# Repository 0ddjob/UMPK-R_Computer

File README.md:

# УМПК-Р (UMPK-R) Computer
Information about the Soviet Ukrainian computer based on the Soviet homebrew computer called the [РАДИО-86РК](https://github.com/skiselev/radio-86rk) (RADIO-86RK).  I'll refer to it as the "RK" (Radio Computer) for the rest of this description.  This computer utilised the Soviet equivalent of the Intel 8080A called the КР580ВМ80А.<br>

УМПК-Р = Универсальный МикроПроцессорный Комплект - Радио (Universal MicroProcessor Kit - Radio)<br>

My computer doesn't work so I need to troubleshoot, hence this translation work.  The Soviets were very good in including schematics & documentation how the computer works.<br>

There were quite a few industrially produced clones of the RK design so understanding how it works can help with troubleshooting other machines.<br>

## My YouTube Videos (As of 9-Mar-2025)
- [Part 1: First Look](https://youtu.be/Kr2Yl7z__qQ)
- [Part 2: Trying to get video output](https://youtu.be/anAznSh7gso)
- [Part 3: Video output troubleshooting continues](https://youtu.be/vZf2vCqavNA)
- [Part 4: Faulty DRAM?](https://youtu.be/Y1xS1cXXh0Q)
- [Part 5: Progress, Maybe](https://youtu.be/lffw-Pr39o8)
- [Part 6: Quick Troubleshooting Update](https://youtu.be/sxfEuDL6Sj8)
- [Part 7: New Keyboard](https://youtu.be/CkGMiSZlumM)

## [English Documentation](/Documentation_ENG)
I have done a partial translation (thanks to Grok) of the Operation Manual - original scanned Russian, my cleaned-up Russian and the translated English manuals can be found here.  There are four file types:
- Apple Pages (native)
- PDF
- Rich Text Format
- MS Word

Note that there may be errors in my cleaned-up Russian copy ... some words in the scanned manual disappeared into the page binding!<br>

Question: what on earth is "foiled lavsan" (фольгированный лавсан)?<br>

_"Lavsan" is a Russian trade name for a type of polyester film, chemically known as polyethylene terephthalate (PET). It is similar to materials like Mylar in Western terminology. "Фольгированный" means "foiled" or "coated with foil," indicating that the lavsan film has a thin layer of metal foil (often aluminium) applied to it. In the context of the УМПК-Р keyboard device, this refers to a metallised polyester film used in the membrane keyboard construction, where the foil provides conductive tracks or contacts for key operation._<br>

_So, in technical terms, it could be described as "metallised polyester film" or simply "foiled PET film", depending on the context._

In the English translation I have kept the Soviet/Russian part identifiers rather than transliterate them, but I have included Western equivalent part identifiers as well.<br>

The scanned Russian manual includes the tables & diagrams referred to in the translation.  It also includes a map of the parts on the motherboard.<br>

I have also included some very-roughly machine translated (Google image) pages from the original Soviet RADIO magazine that explain the RK's functionality - I hope to come back and do better translations.<br>

## Memory Layout

## Map of ICs
Due to the complete lack of 14-pin 32kbit DRAMs in the West I have replaced my faulty ones with 4164 64kbit DRAMs.<br>

```
- D1    КР580ГФ24   8224    Clock generator
- D2    КР580ВТ57   8257    DMA controller
- D3    К155ИЕ4     74LS92  Divide-by-12 counter
- D4    К155ЛИ1     74LS08  Quad 2IN AND
- D5    КР580ВМ80А  8080A   CPU
- D6    К155ЛП5     74LS86  Quad 2IN XOR
- D7    К589ИР12    8212    8-bit I/O port
- D8    КР580ВГ75   8275    CRT controller
- D9    К555ИД7     74LS138 1-of-8 decoder/demultiplexer
- D10   К155ЛА8     74LS01  Quad 2IN NAND
- D11   К155ЛН1     74LS04  Hex inverter
- D12   К573РФ2     2716    EPROM (for character data)
- D13   К155ТМ2     74LS74  Dual D-type flip flop
- D14   КР580ВВ55А  8255    Programmable peripheral adaptor
- D15   К155ИР1     74LS95  4-bit shift register
- D16   К155ИР13    74LS198 8-bit shift register
- D17   К555КП11    74LS257 Quad 2IN multiplexer
- D18   К555КП11    74LS257 Quad 2IN multiplexer
- D19   К573РФ5     2716    EPROM (for MONITOR)
- D20   КР565РУ5Д1          32K x 1bit DRAM
- D21   КР565РУ5Д1          32K x 1bit DRAM
- D22   КР565РУ5Д1          32K x 1bit DRAM
- D23   КР565РУ5Д1          32K x 1bit DRAM
- D24   КР580ВВ55А  8255    Programmable peripheral adaptor
- D25   КР565РУ5Д1          32K x 1bit DRAM
- D26   КР565РУ5Д1          32K x 1bit DRAM
- D27   КР565РУ5Д1          32K x 1bit DRAM
- D28   КР565РУ5Д1          32K x 1bit DRAM
- D29   К553УД2     LM301   Op. Amp.
```
## [Replacement Keyboard](/Replacement_Keyboard)
I suspect that after 40-odd years (mid-1980s to mid-2020s) that the "foiled lavsan" membrane keyboard has started to malfunction.  To replace it I have designed a new board using Cherry MX keyswitches.  You will need to recover the СНП58-32 connector and the speaker from the original keyboard PCB, otherwise it uses readily available parts.<br>

My initial design doesn't re-use the black, clip-on fascia - it expects you to have just the plain, naked PCB ... that's my preference.  But I guess it would be good to design one for the fascia as well ... <br>

### Status
24-Mar-2025: Submitted to PCBWAY for fabrication
20-Apr-2025: Built first board, mostly okay, some revisions required

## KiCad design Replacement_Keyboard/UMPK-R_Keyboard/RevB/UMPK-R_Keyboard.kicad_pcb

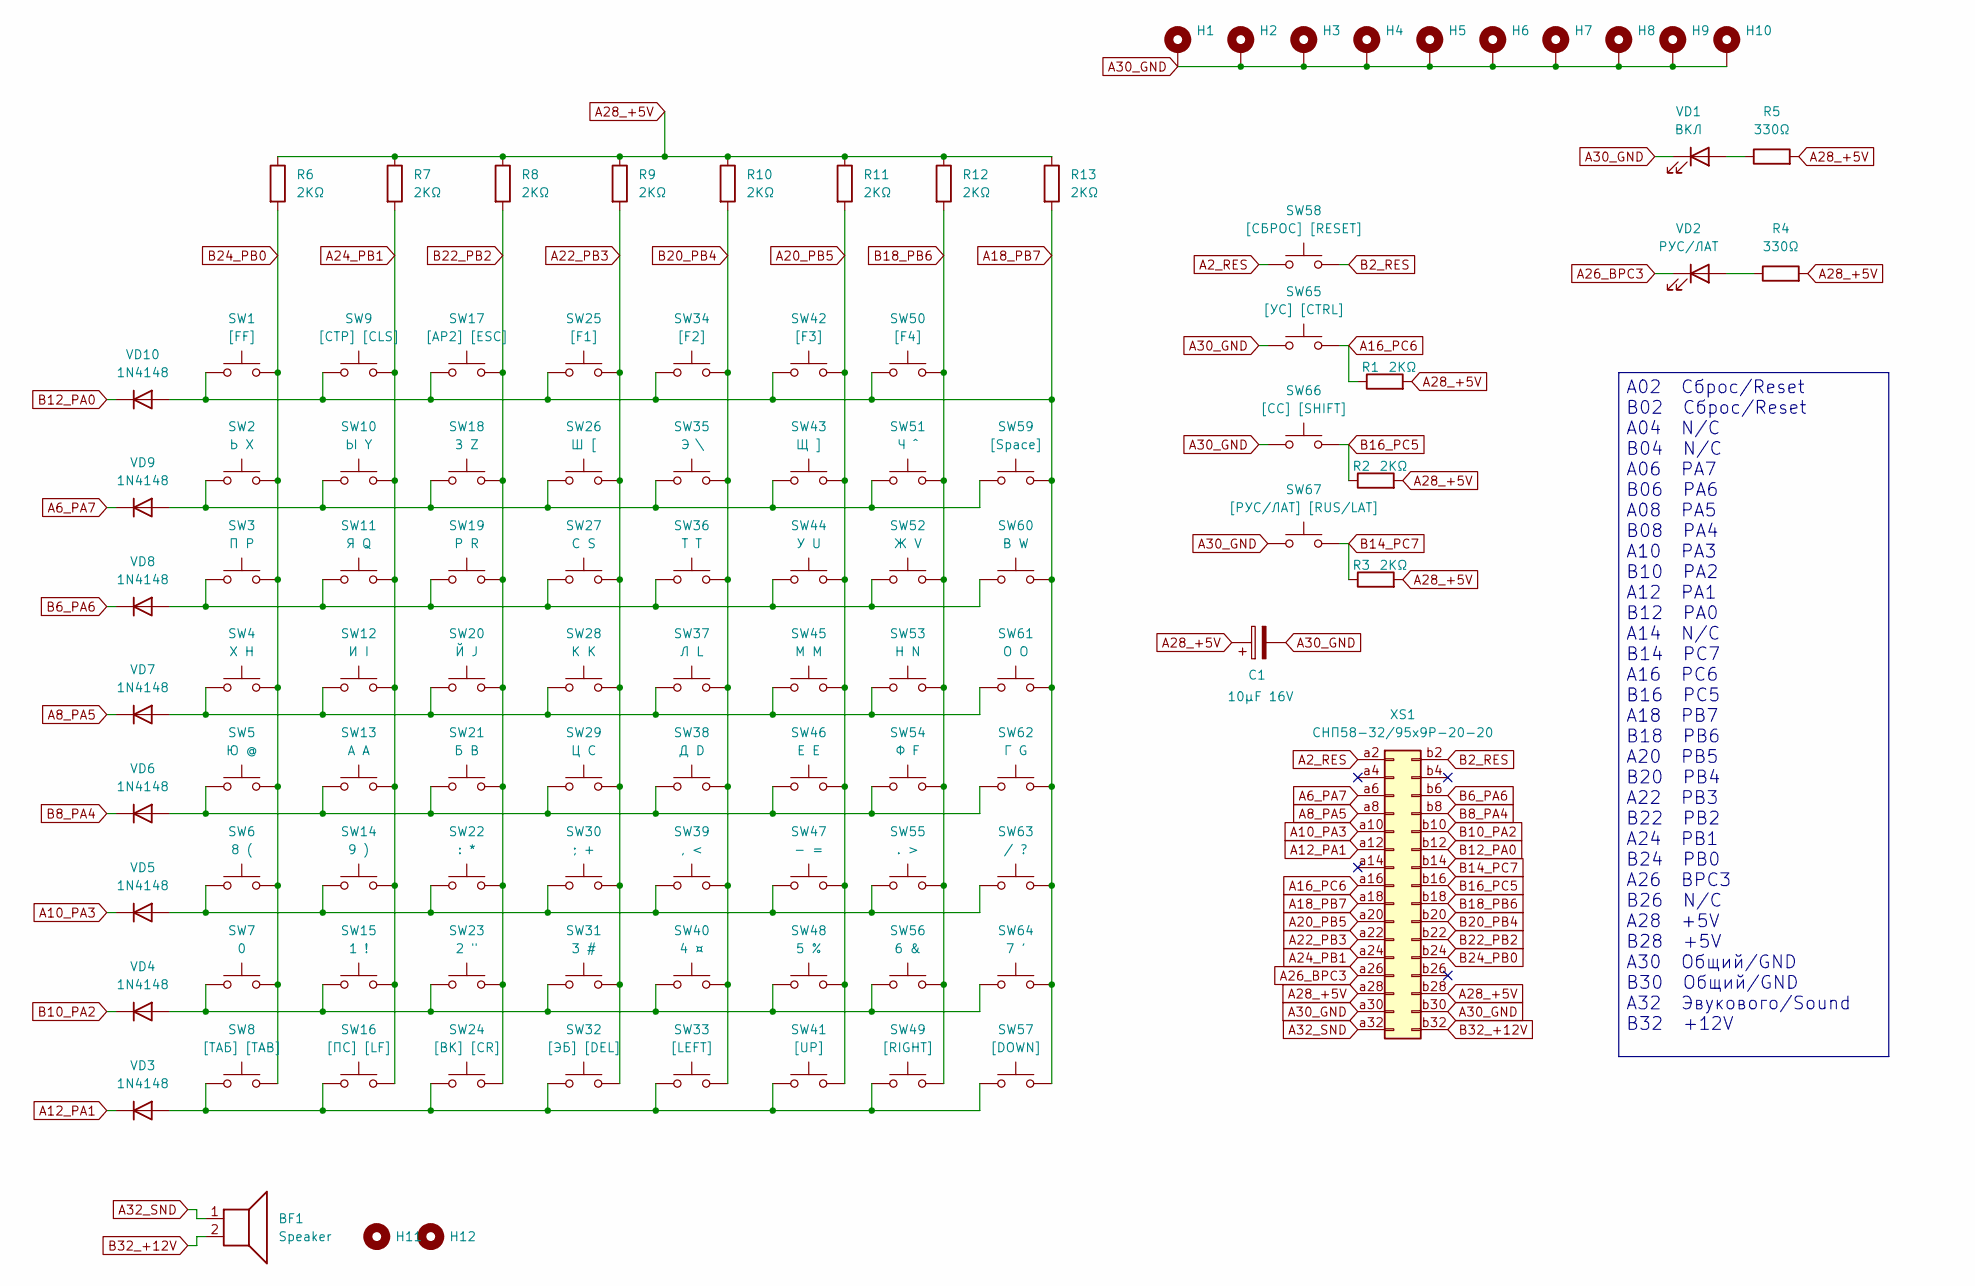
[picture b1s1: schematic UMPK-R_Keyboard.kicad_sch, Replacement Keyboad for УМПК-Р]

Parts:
BF1: Speaker; PinHeader_1x02_P2.54mm_Vertical
C1: 10µF 16V; CP_Radial_D5.0mm_P2.50mm
H1, H2, H3, H4, H5, H6, H7, H8, H9, H10: MountingHole_Pad; MountingHole_3.2mm_M3_Pad
H11, H12: MountingHole; MountingHole_3.2mm_M3
R1, R2, R3, R6, R7, R8, R9, R10, R11, R12, R13: 2KΩ; R_Axial_DIN0207_L6.3mm_D2.5mm_P7.62mm_Horizontal
R4, R5: 330Ω; R_Axial_DIN0207_L6.3mm_D2.5mm_P7.62mm_Horizontal
SW1: [FF]; SW_Cherry_MX_PCB_1.00u
SW2: Ь X; SW_Cherry_MX_PCB_1.00u
SW3: П P; SW_Cherry_MX_PCB_1.00u
SW4: Х H; SW_Cherry_MX_PCB_1.00u
SW5: Ю @; SW_Cherry_MX_PCB_1.00u
SW6: 8 (; SW_Cherry_MX_PCB_1.00u
SW7: 0; SW_Cherry_MX_PCB_1.00u
SW8: [ТАБ] [TAB]; SW_Cherry_MX_PCB_1.00u
SW9: [СТР] [CLS]; SW_Cherry_MX_PCB_1.00u
SW10: Ы Y; SW_Cherry_MX_PCB_1.00u
SW11: Я Q; SW_Cherry_MX_PCB_1.00u
SW12: И I; SW_Cherry_MX_PCB_1.00u
SW13: А A; SW_Cherry_MX_PCB_1.00u
SW14: 9 ); SW_Cherry_MX_PCB_1.00u
SW15: 1 !; SW_Cherry_MX_PCB_1.00u
SW16: [ПС] [LF]; SW_Cherry_MX_PCB_1.00u
SW17: [АР2] [ESC]; SW_Cherry_MX_PCB_1.00u
SW18: З Z; SW_Cherry_MX_PCB_1.00u
SW19: Р R; SW_Cherry_MX_PCB_1.00u
SW20: Й J; SW_Cherry_MX_PCB_1.00u
SW21: Б B; SW_Cherry_MX_PCB_1.00u
SW22: : *; SW_Cherry_MX_PCB_1.00u
SW23: 2 "; SW_Cherry_MX_PCB_1.00u
SW24: [ВК] [CR]; SW_Cherry_MX_PCB_2.00u
SW25: [F1]; SW_Cherry_MX_PCB_1.00u
SW26: Ш [; SW_Cherry_MX_PCB_1.00u
SW27: С S; SW_Cherry_MX_PCB_1.00u
SW28: К K; SW_Cherry_MX_PCB_1.00u
SW29: Ц C; SW_Cherry_MX_PCB_1.00u
SW30: ; +; SW_Cherry_MX_PCB_1.00u
SW31: 3 #; SW_Cherry_MX_PCB_1.00u
SW32: [ЭБ] [DEL]; SW_Cherry_MX_PCB_1.00u
SW33: [LEFT]; SW_Cherry_MX_PCB_1.00u
SW34: [F2]; SW_Cherry_MX_PCB_1.00u
SW35: Э \; SW_Cherry_MX_PCB_1.00u
SW36: Т T; SW_Cherry_MX_PCB_1.00u
SW37: Л L; SW_Cherry_MX_PCB_1.00u
SW38: Д D; SW_Cherry_MX_PCB_1.00u
SW39: , <; SW_Cherry_MX_PCB_1.00u
SW40: 4 ¤; SW_Cherry_MX_PCB_1.00u
SW41: [UP]; SW_Cherry_MX_PCB_1.00u
SW42: [F3]; SW_Cherry_MX_PCB_1.00u
SW43: Щ ]; SW_Cherry_MX_PCB_1.00u
SW44: У U; SW_Cherry_MX_PCB_1.00u
SW45: М M; SW_Cherry_MX_PCB_1.00u
SW46: Е E; SW_Cherry_MX_PCB_1.00u
SW47: - =; SW_Cherry_MX_PCB_1.00u
SW48: 5 %; SW_Cherry_MX_PCB_1.00u
SW49: [RIGHT]; SW_Cherry_MX_PCB_1.00u
SW50: [F4]; SW_Cherry_MX_PCB_1.00u
SW51: Ч ^; SW_Cherry_MX_PCB_1.00u
SW52: Ж V; SW_Cherry_MX_PCB_1.00u
SW53: Н N; SW_Cherry_MX_PCB_1.00u
SW54: Ф F; SW_Cherry_MX_PCB_1.00u
SW55: . >; SW_Cherry_MX_PCB_1.00u
SW56: 6 &; SW_Cherry_MX_PCB_1.00u
SW57: [DOWN]; SW_Cherry_MX_PCB_1.00u
SW58: [СБРОС] [RESET]; SW_Cherry_MX_PCB_1.00u
SW59: [Space]; SW_Cherry_MX_PCB_2.25u
SW60: В W; SW_Cherry_MX_PCB_1.00u
SW61: О O; SW_Cherry_MX_PCB_1.00u
SW62: Г G; SW_Cherry_MX_PCB_1.00u
SW63: / ?; SW_Cherry_MX_PCB_1.00u
SW64: 7 '; SW_Cherry_MX_PCB_1.00u
SW65: [УС] [CTRL]; SW_Cherry_MX_PCB_1.00u
SW66: [СС] [SHIFT]; SW_Cherry_MX_PCB_1.00u
SW67: [РУС/ЛАТ] [RUS/LAT]; SW_Cherry_MX_PCB_1.00u
VD1: ВКЛ; LED_D5.0mm
VD2: РУС/ЛАТ; LED_D5.0mm
VD3, VD4, VD5, VD6, VD7, VD8, VD9, VD10: 1N4148; D_DO-35_SOD27_P7.62mm_Horizontal
XS1: СНП58-32/95x9P-20-20; DIN41612_B_2x32_Female_Vertical_THT

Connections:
A2_RES: SW58.1, XS1.a2
A6_PA7: VD9.1 (K), XS1.a6
A8_PA5: VD7.1 (K), XS1.a8
A10_PA3: VD5.1 (K), XS1.a10
A12_PA1: VD3.1 (K), XS1.a12
A16_PC6: R1.1, SW65.2, XS1.a16
A18_PB7: R13.2, SW1.1, SW9.1, SW17.1, SW25.1, SW34.1, SW42.1, SW50.1, SW57.2, SW59.2, SW60.2, SW61.2, SW62.2, SW63.2, SW64.2, VD10.2 (A), XS1.a18
A20_PB5: R11.2, SW41.2, SW42.2, SW43.2, SW44.2, SW45.2, SW46.2, SW47.2, SW48.2, XS1.a20
A22_PB3: R9.2, SW25.2, SW26.2, SW27.2, SW28.2, SW29.2, SW30.2, SW31.2, SW32.2, XS1.a22
A24_PB1: R7.2, SW9.2, SW10.2, SW11.2, SW12.2, SW13.2, SW14.2, SW15.2, SW16.2, XS1.a24
A26_BPC3: VD2.1 (K), XS1.a26
A28_+5V: C1.1, R1.2, R2.2, R3.2, R4.2, R5.2, R6.1, R7.1, R8.1, R9.1, R10.1, R11.1, R12.1, R13.1, XS1.a28, XS1.b28
A30_GND: C1.2, H1.1, H2.1, H3.1, H4.1, H5.1, H6.1, H7.1, H8.1, H9.1, H10.1, SW65.1, SW66.1, SW67.1, VD1.1 (K), XS1.a30, XS1.b30
A32_SND: BF1.1, XS1.a32
B2_RES: SW58.2, XS1.b2
B6_PA6: VD8.1 (K), XS1.b6
B8_PA4: VD6.1 (K), XS1.b8
B10_PA2: VD4.1 (K), XS1.b10
B12_PA0: VD10.1 (K), XS1.b12
B14_PC7: R3.1, SW67.2, XS1.b14
B16_PC5: R2.1, SW66.2, XS1.b16
B18_PB6: R12.2, SW49.2, SW50.2, SW51.2, SW52.2, SW53.2, SW54.2, SW55.2, SW56.2, XS1.b18
B20_PB4: R10.2, SW33.2, SW34.2, SW35.2, SW36.2, SW37.2, SW38.2, SW39.2, SW40.2, XS1.b20
B22_PB2: R8.2, SW17.2, SW18.2, SW19.2, SW20.2, SW21.2, SW22.2, SW23.2, SW24.2, XS1.b22
B24_PB0: R6.2, SW1.2, SW2.2, SW3.2, SW4.2, SW5.2, SW6.2, SW7.2, SW8.2, XS1.b24
B32_+12V: BF1.2, XS1.b32
unnamed: R5.1, VD1.2 (A)
unnamed: R4.1, VD2.2 (A)
unnamed: SW8.1, SW16.1, SW24.1, SW32.1, SW33.1, SW41.1, SW49.1, SW57.1, VD3.2 (A)
unnamed: SW7.1, SW15.1, SW23.1, SW31.1, SW40.1, SW48.1, SW56.1, SW64.1, VD4.2 (A)
unnamed: SW6.1, SW14.1, SW22.1, SW30.1, SW39.1, SW47.1, SW55.1, SW63.1, VD5.2 (A)
unnamed: SW5.1, SW13.1, SW21.1, SW29.1, SW38.1, SW46.1, SW54.1, SW62.1, VD6.2 (A)
unnamed: SW4.1, SW12.1, SW20.1, SW28.1, SW37.1, SW45.1, SW53.1, SW61.1, VD7.2 (A)
unnamed: SW3.1, SW11.1, SW19.1, SW27.1, SW36.1, SW44.1, SW52.1, SW60.1, VD8.2 (A)
unnamed: SW2.1, SW10.1, SW18.1, SW26.1, SW35.1, SW43.1, SW51.1, SW59.1, VD9.2 (A)

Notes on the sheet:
A02 Сброс/Reset B02 Сброс/Reset A04 N/C B04 N/C A06 PA7 B06 PA6 A08 PA5 B08 PA4 A10 PA3 B10 PA2 A12 PA1 B12 PA0 A14 N/C B14 PC7 A16 PC6 B16 PC5 A18 PB7 B18 PB6 A20 PB5 B20 PB4 A22 PB3 B22 PB2 A24 PB1 B24 PB0 A26 BPC3 B26 N/C A28 +5V B28 +5V A30 Общий/GND B30 Общий/GND A32 Эвукового/Sound B32 +12V

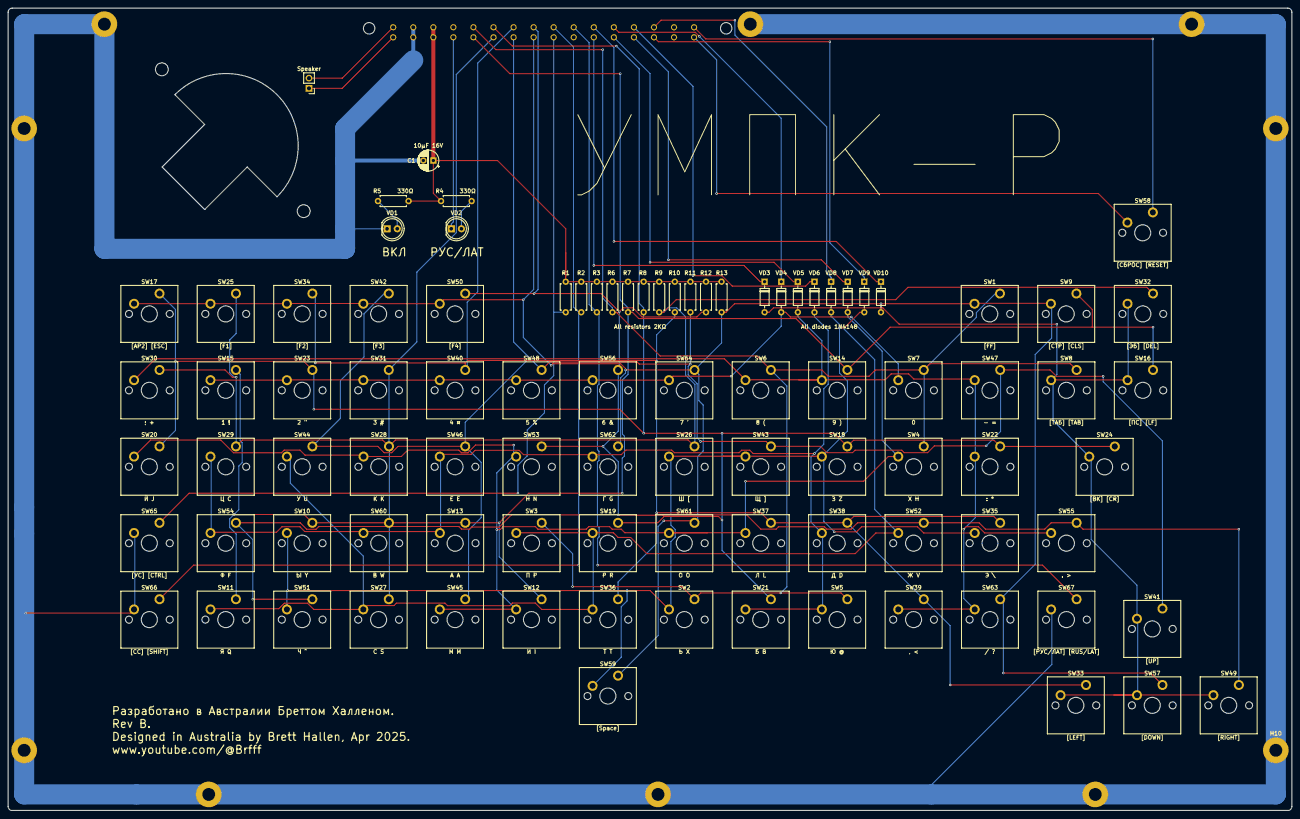
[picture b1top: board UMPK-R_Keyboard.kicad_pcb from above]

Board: 2 copper layers, 320.0 x 200.0 mm, 105 parts (1 on the bottom side), 35 nets.

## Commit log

2025-03-09 Russian updates
2025-03-09 Added original RADIO magazine pages
2025-03-09 Moved documents to own folders
2025-03-09 Added version info to documents
2025-03-09 Added IC part IDs
2025-03-09 Added original RADIO magazine page images (from Sergey's Radio-86RK repository)
2025-03-09 Filename correction
2025-03-09 Added special key information
2025-03-09 Added info about LAVSAN (ЛАВСАН)
2025-03-09 Minor corrections
2025-03-09 Minor improvements in the text
2025-03-09 Added intro, memory layout, sections 1 & 4
2025-03-10 Minor updates
2025-03-10 Added data bus bits to DRAM layout
2025-03-11 Updated circuit layout
2025-03-12 Added section 7, started on section 8
2025-03-24 Initial keyboard design
2025-04-17 Added HTML BOM
2025-05-01 Revising keyboard design
2025-05-01 ENG debugging guide
2025-05-02 Added additional information
2025-05-02 Further improvements to text & layout
2025-05-02 Added test ROM details
